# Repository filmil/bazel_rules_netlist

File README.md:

<!-- SPDX-License-Identifier: Apache-2.0 -->

# hdlf_rules_netlist

Hermetic Bazel rules for circuits written as code.
The build runs a [SKiDL](https://github.com/devbisme/skidl) circuit
script, writes a KiCad netlist that the
[hdlf_rules_kicad](https://github.com/filmil/bazel_rules_kicad) board
rules use, and checks that a board's nets match it.
Every tool comes from a Bazel toolchain, so nothing needs to be installed
on the machine, and two builds give byte-identical outputs.

Only Linux x86_64 hosts are supported in v1. Elsewhere the build fails at
analysis time with a message that says so.

The rules are documented in [docs/defs.md](docs/defs.md), generated from
their sources.

## Using it

`MODULE.bazel`:

```starlark
bazel_dep(name = "hdlf_rules_netlist", version = "0.0.1")
bazel_dep(name = "hdlf_rules_kicad", version = "0.0.1")
```

Under Bazel 8, rules_python asks for a C++ toolchain even though nothing
is compiled, so a build that finds none on the host must bring one. The
self-contained zig toolchain is enough; Bazel 9 does not ask:

```starlark
bazel_dep(name = "hermetic_cc_toolchain", version = "4.3.0")

zig_toolchains = use_extension("@hermetic_cc_toolchain//toolchain:ext.bzl", "toolchains")
use_repo(zig_toolchains, "zig_sdk")

register_toolchains("@zig_sdk//toolchain:linux_amd64_gnu.2.31")
```

`.bazelrc`, while the module is only in the filmil registry:

```
common --registry=https://raw.githubusercontent.com/filmil/bazel-registry/main
common --registry=https://bcr.bazel.build
```

SKiDL needs no Python on the host and no flag in your `.bazelrc`: it runs
on rules_python's hermetic CPython 3.12, with the wheels that
`requirements_lock.txt` pins by hash and the KiCad 9.0.9 symbol libraries
that hdlf_rules_kicad pins.

## From a circuit script to a checked board

`integration/skidl_netlist` is this whole path, as a user writes it. A
circuit script builds its circuit with SKiDL. It need not call
`generate_netlist()`; the rule writes the netlist:

```python
# circuit.py: a LED and its resistor on a 3.3 V connector.
from skidl import Net, Part

vcc = Net("+3V3")
gnd = Net("GND")

j1 = Part("Connector_Generic", "Conn_01x02", ref="J1", value="Power",
          footprint="Connector_PinHeader_2.54mm:PinHeader_1x02_P2.54mm_Vertical")
r1 = Part("Device", "R", ref="R1", value="1k",
          footprint="Resistor_SMD:R_0603_1608Metric")
d1 = Part("Device", "LED", ref="D1", value="LED",
          footprint="LED_SMD:LED_0603_1608Metric")

vcc += j1[1], r1[1]
gnd += j1[2], d1["K"]
r1[2] += d1["A"]
```

Parts come from the SKiDL toolchain's symbol libraries, and from nowhere
else: by default, the KiCad 9.0.9 libraries that hdlf_rules_kicad pins
(see "Toolchains" below to bring others).
Then the BUILD file:

```starlark
load("@hdlf_rules_kicad//kicad:defs.bzl", "kicad_gerbers", "kicad_pcb")
load("@hdlf_rules_netlist//netlist:defs.bzl", "determinism_test", "netlist_parity_test", "skidl_netlist")

# circuit.py -> netlist.net
skidl_netlist(
    name = "netlist",
    src = "circuit.py",
    deps = ["parts.py"],  # modules circuit.py imports, if any
)

# The board, laid out in KiCad against that netlist.
kicad_pcb(
    name = "pcb",
    board = "main.kicad_pcb",
    netlist = ":netlist",
)

# The board joins exactly the pins the netlist joins.
netlist_parity_test(
    name = "parity_test",
    size = "small",
    board = "main.kicad_pcb",
    netlist = ":netlist",
)

# The same netlist on two builds.
determinism_test(
    name = "netlist_determinism_test",
    size = "small",
    target = ":netlist",
)

# Fab outputs, from hdlf_rules_kicad.
kicad_gerbers(
    name = "gerbers",
    pcb = ":pcb",
)
```

`bazel test //...` runs the SKiDL script, checks the board against the
netlist, and checks that the netlist is the same twice.

## The rules

Load every rule from `@hdlf_rules_netlist//netlist:defs.bzl`.
[docs/defs.md](docs/defs.md) has every attribute.

### skidl_netlist

A KiCad netlist, `<name>.net`, from a SKiDL circuit script, for
`kicad_pcb(netlist = ...)`. The netlist is the same on every build: the
runner fixes its header (the source is the script's workspace path, the
date 1970-01-01, the tool "SKiDL (3.0.0)") and each part's file reference,
and seeds the random generator that SKiDL tags parts with. A component's
time stamp, which links it to its footprint on the board, comes from its
tag, so give `tag=` to a part whose board link must stay put when you add
or move parts before it:

```python
r1 = Part("Device", "R", ref="R1", value="1k", tag="r1")
```

A script that makes no parts fails.

### netlist_parity_test

Checks that a board's nets join the pins a netlist's nets join. Nets are
compared by their pins, not their names, so SKiDL's `N$1` and a
schematic's `Net-(D1-A)` match when they join the same pins. It fails,
naming each difference, on a missing net or pad, a net split over two
board nets, two netlist nets shorted on the board, a pin with pads on two
nets, or a component with no footprint. It reads netlists of
`skidl_netlist` and of hdlf_rules_kicad's `kicad_netlist`.

`want_error` turns it into a known-bad test, for a board that must fail:

```starlark
netlist_parity_test(
    name = "missing_net_test",
    size = "small",
    board = "missing_net.kicad_pcb",
    netlist = ":netlist",
    want_error = "pin D1.2 is on no net of the board",
)
```

### determinism_test

Builds a target twice, in two configurations that change nothing but the
output paths, and fails if any output file differs:

```starlark
determinism_test(
    name = "netlist_determinism_test",
    size = "small",
    target = ":netlist",
)
```

### swap_test

Builds targets with every tool swapped for a stub, and checks that each
output came from the toolchain's tool (spec "Toolchains", requirement 7):

```starlark
swap_test(
    name = "swap_test",
    size = "small",
    targets = [":netlist"],
)
```

### Toolchains: skidl_toolchain, tool_toolchain, SkidlToolchainInfo

The module registers its SKiDL toolchain; most users need nothing more.
To bring other symbol libraries, or another build of the SKiDL runner,
define your own in a BUILD file, here `//toolchains/BUILD.bazel`:

```starlark
load("@hdlf_rules_netlist//netlist:defs.bzl", "skidl_toolchain")

skidl_toolchain(
    name = "my_skidl_impl",
    runner = "@hdlf_rules_netlist//netlist:skidl_runner",
    symbols = "//third_party/kicad:symbols",  # .kicad_sym files in one directory
)

toolchain(
    name = "my_skidl",
    toolchain = ":my_skidl_impl",
    toolchain_type = "@hdlf_rules_netlist//netlist:skidl_toolchain_type",
)
```

and register it in your `MODULE.bazel`. The root module's toolchains come
before those of its dependencies, so Bazel picks yours:

```starlark
register_toolchains("//toolchains:my_skidl")
```

`SkidlToolchainInfo` is what that toolchain gives a rule: the KiCad
version and the symbol libraries. `tool_toolchain` makes a toolchain of
named tools for `run_tool`, the one place where this module's rules start
a tool.

## Schematics from code

A SKiDL circuit gives a netlist, not a `.kicad_sch`, so it gets no ERC and
no schematic renders. For now that stays so: SKiDL 3.0.0 writes KiCad 9
and 10 schematics, but they differ from build to build (random UUIDs,
today's date, and wire routing that changes even with every seed fixed),
and the sheet it wrote fails hdlf_rules_kicad's ERC. Issue #12 has the
details; it can be looked at again when SKiDL's schematizer is
deterministic. Until then, `netlist_parity_test` against the board, with
hdlf_rules_kicad's DRC and board renders, checks a circuit written as code.

## Building

```sh
bazel build //...
bazel test //...
cd integration && bazel test //...
```

After changing a `.bzl` file, regenerate the documentation with
`bazel run //docs:update_docs`.
Format with `bazel run //tools:buildifier`; CI fails when
`bazel run //tools:buildifier_check` or the hermeticity lint
(`bazel run //tools/lint`) does.
`bazel run //tools:requirements.update` writes `requirements_lock.txt`
from `requirements.in`; `bazel run //tools:mirror` checks the mirrored
wheels (`tools/mirror/README.md`).

## Releasing

The operator runs the `Tag and Release` workflow
(`.github/workflows/tag-and-release.yml`, `workflow_dispatch`).
It picks the next version from the conventional commits since the last
tag, makes the tag, the release and its source archive, and opens one
pull request on the filmil registry and one on the Bazel Central Registry.
It needs the repository secret `BCR_PUBLISH_TOKEN`.

None of the modules published here are published with any sort of guarantee
whatsoever. Use at your own risk.

See the overall description at the [project page][pp].

[pp]: https://hdlfactory.com/post/2025/09/29/getting-ready-for-the-brave-new-bazel-modules-world/

## Licenses

This repository is under the Apache License 2.0 (`LICENSE`). The build
downloads the prebuilts below, each pinned by its hash. They are tools of
the build: none of them is copied into the netlists or checks it writes.

**Mirrored here.** PyPI has only the sdists of these pure-Python packages;
their wheels are built from those, as `tools/mirror/README.md` says, and
mirrored in this repository's release
[mirror-skidl-3.0.0](https://github.com/filmil/bazel_rules_netlist/releases/tag/mirror-skidl-3.0.0).

| Package | Version | License | Source |
|---|---|---|---|
| skidl | 3.0.0 | MIT | https://github.com/devbisme/skidl |
| kinet2pcb | 1.1.4 | MIT | https://github.com/devbisme/kinet2pcb |
| hierplace | 1.1.0 | MIT | https://github.com/devbisme/HierPlace |

**Wheels from PyPI**, pinned by hash in `requirements_lock.txt`:

| Package | Version | License | Source |
|---|---|---|---|
| cffi | 2.1.1 | MIT-0 | https://pypi.org/project/cffi/2.1.1/ |
| contourpy | 1.4.0 | BSD-3-Clause | https://pypi.org/project/contourpy/1.4.0/ |
| cycler | 0.12.1 | BSD | https://pypi.org/project/cycler/0.12.1/ |
| deprecation | 2.1.0 | Apache-2.0 | https://pypi.org/project/deprecation/2.1.0/ |
| diskcache | 5.6.3 | Apache-2.0 | https://pypi.org/project/diskcache/5.6.3/ |
| fonttools | 4.68.0 | MIT | https://pypi.org/project/fonttools/4.68.0/ |
| graphviz | 0.21 | MIT | https://pypi.org/project/graphviz/0.21/ |
| h5py | 3.16.0 | BSD-3-Clause | https://pypi.org/project/h5py/3.16.0/ |
| inspice | 1.7.0.7 | GPL-3.0-or-later | https://pypi.org/project/inspice/1.7.0.7/ |
| kiwisolver | 1.5.1 | BSD | https://pypi.org/project/kiwisolver/1.5.1/ |
| markdown-it-py | 4.2.0 | MIT | https://pypi.org/project/markdown-it-py/4.2.0/ |
| matplotlib | 3.11.2 | PSF-based (matplotlib license) | https://pypi.org/project/matplotlib/3.11.2/ |
| mdurl | 0.1.2 | MIT | https://pypi.org/project/mdurl/0.1.2/ |
| numpy | 2.5.4 | BSD-3-Clause AND 0BSD AND MIT AND Zlib AND CC0-1.0 | https://pypi.org/project/numpy/2.5.4/ |
| packaging | 26.3 | Apache-2.0 OR BSD-2-Clause | https://pypi.org/project/packaging/26.3/ |
| pillow | 13.0.0 | MIT-CMU | https://pypi.org/project/pillow/13.0.0/ |
| ply | 3.11 | BSD | https://pypi.org/project/ply/3.11/ |
| pycparser | 3.12 | BSD-3-Clause | https://pypi.org/project/pycparser/3.12/ |
| pygments | 2.21.0 | BSD-2-Clause | https://pypi.org/project/pygments/2.21.0/ |
| pyparsing | 3.3.3 | MIT | https://pypi.org/project/pyparsing/3.3.3/ |
| python-dateutil | 3.0.0 | Apache-2.0 AND BSD-3-Clause | https://pypi.org/project/python-dateutil/3.0.0/ |
| pyyaml | 6.0.3 | MIT | https://pypi.org/project/pyyaml/6.0.3/ |
| rich | 15.0.0 | MIT | https://pypi.org/project/rich/15.0.0/ |
| schematizer | 0.2.0 | MIT | https://pypi.org/project/schematizer/0.2.0/ |
| simp-sexp | 0.3.1 | MIT | https://pypi.org/project/simp-sexp/0.3.1/ |
| six | 1.17.0 | MIT | https://pypi.org/project/six/1.17.0/ |
| tzdata | 2026.6 | Apache-2.0 | https://pypi.org/project/tzdata/2026.6/ |

inspice is GPL-3.0-or-later. SKiDL 3.0.0 requires it on Python 3.11 and
later; it is fetched from PyPI at build time and runs only inside the
build, and nothing of it is in this repository's sources, releases or
outputs.

**Other prebuilts:**

| What | Version | License | Source |
|---|---|---|---|
| CPython, from rules_python 2.4.6 | 3.12.16 | PSF-2.0 | https://github.com/astral-sh/python-build-standalone |
| KiCad symbol libraries, through hdlf_rules_kicad | 9.0.9 | CC-BY-SA-4.0 with the KiCad libraries exception | https://gitlab.com/kicad/libraries/kicad-symbols |
| Go SDK, from rules_go 0.64.2, for the Go helpers | 1.26.7 | BSD-3-Clause | https://go.dev/dl/ |

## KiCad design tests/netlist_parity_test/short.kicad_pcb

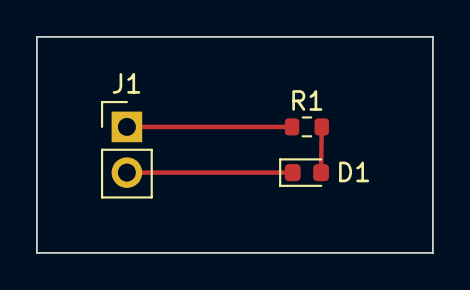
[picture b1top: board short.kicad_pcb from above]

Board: 2 copper layers, 22.0 x 12.0 mm, 3 parts (0 on the bottom side), 2 nets.

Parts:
D1: LED; LED_0603_1608Metric
J1: Power; PinHeader_1x02_P2.54mm_Vertical
R1: 1k; R_0603_1608Metric

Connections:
+3V3: D1.1, J1.1, R1.1
unnamed: D1.2, R1.2

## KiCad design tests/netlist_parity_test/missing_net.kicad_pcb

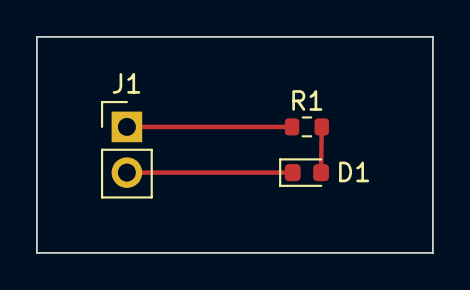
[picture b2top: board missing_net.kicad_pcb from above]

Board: 2 copper layers, 22.0 x 12.0 mm, 3 parts (0 on the bottom side), 2 nets.

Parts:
D1: LED; LED_0603_1608Metric
J1: Power; PinHeader_1x02_P2.54mm_Vertical
R1: 1k; R_0603_1608Metric

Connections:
+3V3: J1.1, R1.1
GND: D1.1, J1.2
